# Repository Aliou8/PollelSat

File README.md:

# 

## 📘 Description

Ce projet a pour objectif la conception et la réalisation complète d’un CubeSat au format **1U**.
Il couvre l’ensemble du cycle de développement :

* **Conception 3D** de la structure
* **Développement hardware** (cartes, alimentation, capteurs, communication)
* **Développement software** embarqué
* Intégration, tests et documentation

L’objectif est de créer une plateforme expérimentale ouverte, évolutive et accessible.

---

## 🛰️ Objectifs du projet

* Développer une architecture CubeSat fonctionnelle en open-source
* Expérimenter l’ingénierie spatiale à petite échelle
* Créer un modèle reproductible pour étudiants et makers
* Documenter toutes les étapes : mécanique, électronique, firmware, protocoles…

---

## 🧩 Structure du dépôt

```
/3D/              → Fichiers de conception mécanique (CAD)
/hardware/        → Schémas, PCB, BOM
/software/        → Code embarqué, drivers, protocoles
/docs/            → Documentation technique
/tests/           → Scripts et procédures de tests
```

---

## 🛠️ Technologies utilisées

### Conception 3D
La conception mécanique du CubeSat 1U est entièrement réalisée sur **Onshape**. Dans un premier temps, il est nécessaire de créer le cadre qui respecte les contraintes du CubeSat (voir la [spécification CubeSat](docs/CubeSatSpecification.pdf)).
# 

### 🔧 Hardware

* Microcontrôleur **STM32H7** et **Raspberry PI CM4**
* Capteurs IMU, caméras et modules de télécommunication
* Systèmes d’alimentation **Battery** + **PV**
   | Composant       | Png | Schéma      |
  |:-----------|:---:|------------:|
  |  EPS     |   | [Kicad_sch](hardware/EPS/eps.pdf) |
  |  Battery     |   | [Kicad_sch](hardware/BatteryConnector/BatteryConnector.pdf) |

* Systeme Radio **CC1312R1** à 915 MHz
  | Composant       | Png | Schéma      |
  |:-----------|:---:|------------:|
  |  Radio   |   | [Kicad_sch](hardware/RADIO/radio.pdf) |

### 💻 Software

* Firmware en C/C++
* Outils de simulation
* Protocoles de communication embarqués

---

## 📝 Roadmap

* [ ] Conception complète mécanique 1U
* [ ] Prototype des premiers PCB
* [ ] Développement firmware de base
* [ ] Système de télécommunication minimal
* [ ] Tests thermiques & vibration

---

## 🤝 Contribution

Les contributions sont les bienvenues !
Merci de suivre les pull requests et issues du dépôt.

---

## 📜 Licence

**GNU GPL v3**
Ce projet est open-source et distribué sous licence GNU GPL version 3.
Vous êtes libre de l’utiliser, le modifier et le redistribuer tant que la licence reste préservée.

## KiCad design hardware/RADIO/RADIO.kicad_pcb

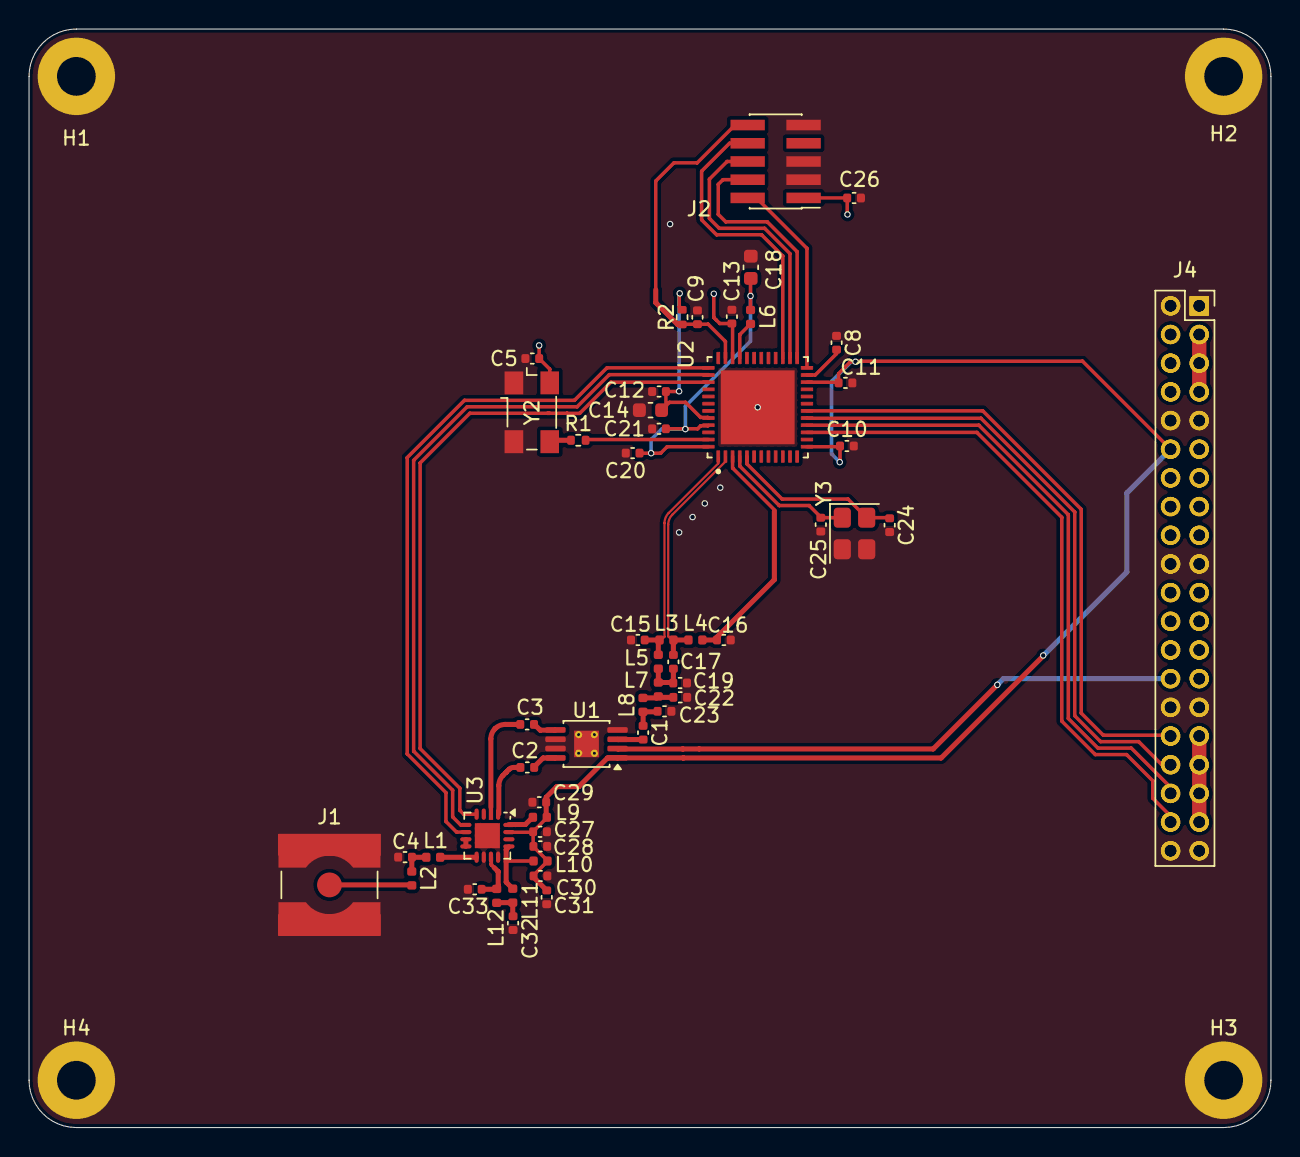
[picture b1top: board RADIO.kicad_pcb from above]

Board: 2 copper layers, 86.6 x 76.6 mm, 58 parts (1 on the bottom side), 60 nets.

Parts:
C1, C2, C3, C16: 100p; C_0402_1005Metric
C4, C33: 2.4p; C_0402_1005Metric
C5, C8, C9, C10, C11, C12, C13, C20, C21, C24, C25, C26: 0.1u; C_0402_1005Metric
C14, C18: 22u; C_0603_1608Metric
C15, C17: 3.6p; C_0402_1005Metric
C19: 2.7p; C_0402_1005Metric
C22: 6.2p; C_0402_1005Metric
C23: 3p; C_0402_1005Metric
C27, C30: 4.7u; C_0402_1005Metric
C28: 10n; C_0402_1005Metric
C29: 120p; C_0402_1005Metric
C31: 33p; C_0402_1005Metric
C32: 10p; C_0402_1005Metric
H1, H2, H3, H4: MountingHole_Pad; MountingHole_2.7mm_M2.5_Pad
J1: SMA ANT; SMA_Amphenol_132134-10_Vertical
J2: Conn_ARM_JTAG_SWD_10; PinHeader_2x05_P1.27mm_Vertical_SMD
J3: Conn; PinHeader_2x20_P2.00mm_Vertical
J4: Conn; PinSocket_2x20_P2.00mm_Vertical
L1, L2: 5.6n; L_0402_1005Metric
L3: 27n; L_0402_1005Metric
L4, L5: 7.5n; L_0402_1005Metric
L6, L7, L8, L10: 6.8n; L_0402_1005Metric
L9: 0.6n; L_0402_1005Metric
L11, L12: 2.7n; L_0402_1005Metric
R1: 100; R_0402_1005Metric
R2: 10K; R_0402_1005Metric
U1: MASWSS0178; MSOP-8-1EP_3x3mm_P0.65mm_EP1.73x1.85mm_ThermalVias
U2: CC1312R1F3RGZT; QFN50P700X700X100-49N
U3: SKY66420-11; UQFN-16-1EP_3x3mm_P0.5mm_EP1.75x1.75mm
Y2: FT5HN; Oscillator_SMD_Fox_FT5H_5.0x3.2mm
Y3: 32.768kHz; Crystal_SMD_3225-4Pin_3.2x2.5mm

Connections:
+3.3V: J3.3, J3.5, J3.7, J4.3, J4.5, J4.7
+5V: J3.31, J3.33, J3.35, J3.37, J4.31, J4.33, J4.35, J4.37
/Clock Oscillator/Clock_in: R1.2, U2.47 (X48M_P)
/Front-End Module/ANT: L1.1, U3.9 (ANT)
/Front-End Module/CPS: U2.38 (DIO_25), U3.5 (CPS)
/Front-End Module/CSD: U2.39 (DIO_26), U3.4 (CSD)
/Front-End Module/CTX: U2.37 (DIO_24), U3.6 (CTX)
/Front-End Module/RX: C3.2, U3.2 (RX)
/Front-End Module/TX: C2.2, U3.1 (TX)
/Front-End Module/TX_IN: C33.2, L12.2, U3.11 (TX_IN)
/INTER CONNECTOR/Pin_2b: J3.4, J4.4
/INTER CONNECTOR/Pin_3b: J3.6, J4.6
/INTER CONNECTOR/Pin_4b: J3.8, J4.8
/INTER CONNECTOR/Pin_6a: J3.11, J4.11
/INTER CONNECTOR/Pin_7a: J3.13, J4.13
/INTER CONNECTOR/Pin_7b: J3.14, J4.14
/INTER CONNECTOR/Pin_8a: J3.15, J4.15
/INTER CONNECTOR/Pin_8b: J3.16, J4.16
/INTER CONNECTOR/Pin_9a: J3.17, J4.17
/INTER CONNECTOR/Pin_9b: J3.18, J4.18
/INTER CONNECTOR/Pin_11a: J3.21, J4.21
/INTER CONNECTOR/Pin_11b: J3.22, J4.22
/INTER CONNECTOR/Pin_12a: J3.23, J4.23
/INTER CONNECTOR/Pin_12b: J3.24, J4.24
/INTER CONNECTOR/Pin_13a: J3.25, J4.25
/INTER CONNECTOR/Pin_13b: J3.26, J4.26
/INTER CONNECTOR/Pin_14a: J3.27, J4.27
/INTER CONNECTOR/Pin_16b: J3.32, J4.32, U2.18 (DIO_12)
/INTER CONNECTOR/Pin_17b: J3.34, J4.34, U2.17 (DIO_11)
/INTER CONNECTOR/Pin_18b: J3.36, J4.36, U2.16 (DIO_1O)
/INTER CONNECTOR/Pin_19b: J3.38, J4.38, U2.15 (DIO_9)
/JTAG/JTAG_TCKC: J2.4 (SWCLK/TCK), U2.25 (JTAG_TCKC)
/JTAG/JTAG_TDI: J2.8 (NC/TDI), U2.27 (DIO_17)
/JTAG/JTAG_TDO: J2.6 (SWO/TDO), U2.26 (DIO_16)
/JTAG/JTAG_TMSC: J2.2 (SWDIO/TMS), U2.24 (JTAG_TMSC)
/JTAG/RESET: C9.1, J2.10 (~RESET), R2.1, U2.35 (RESET_N)
/RD_3.3V: C5.1, C10.1, C11.1, C12.1, C13.1, C14.1, C26.1, C27.2, C28.2, C29.2, C30.1, C31.1, J2.1 (VTref), J3.12, J4.12, L9.1, L10.1, R2.2, U1.1 (CTL1), U2.13 (VDDSZ), U2.22 (VDD83), U2.34 (VDDS_DCDC), U2.44 (VDDS), U3.15 (VCCO), Y2.4 (VDD)
/RF_CTRL: J3.28, J4.28, U1.2 (CTL2)
/Transceiver RF/DCDC_SW: L6.1, U2.33 (DCDC_SW)
/Transceiver RF/RF_N: C17.2, L3.2, L4.1, U2.2 (RF_N)
/Transceiver RF/RF_P: C15.1, L3.1, L5.2, U2.1 (RF_P)
/Transceiver RF/RF_SIGNAL: C1.1, C23.1, L8.1
/Transceiver RF/VDDR: C18.1, C20.1, C21.1, L6.2, U2.45 (VDDR), U2.48 (VDDR_RF)
/Transceiver RF/x32_in: C25.1, U2.4 (X32K_Q1), Y3.1
/Transceiver RF/x32_out: C24.1, U2.5 (X32K_Q2), Y3.4
GND: C4.1, C5.2, C8.1, C9.2, C10.2, C11.2, C12.2, C13.2, C14.2, C15.2, C16.2, C18.2, C19.2, C20.2, C21.2, C22.2, C23.2, C24.2, C25.2, C26.2, C27.1, C28.1, C29.1, C30.2, C31.2, C32.1, C33.1, H1.1, H2.1, H3.1, H4.1, J1.2 (Ext), J2.3 (GND), J2.5 (GND), J2.9 (GNDDetect), J3.1, J3.2, J3.9, J3.10, J3.19, J3.20, J3.29, J3.30, J3.39, J3.40, J4.1, J4.2, J4.9, J4.10, J4.19, J4.20, J4.29, J4.30, J4.39, J4.40, U1.4 (GND), U1.6 (GND), U1.7 (GND), U1.9 (GND), U2.49 (PAD), U3.10 (GND), U3.12 (GND), U3.17 (PAD), Y2.1 (GND), Y2.2 (GND), Y3.2, Y3.3
unnamed: C4.2, L1.2, L2.1
unnamed: C17.1, C19.1, L5.1, L7.2
unnamed: C22.1, L7.1, L8.2
unnamed: C32.2, L11.2, L12.1
unnamed: J1.1 (In), L2.2
unnamed: C2.1, U1.8 (RF1)
unnamed: C3.1, U1.5 (RF2)
unnamed: C1.2, U1.3 (RFC)
unnamed: C8.2, U2.23 (DCOUPL)
unnamed: C16.1, L4.2, U2.3 (RX_TX)
unnamed: U3.7 (LNA_IN), U3.8 (RX_FLT)
unnamed: L10.2, L11.1, U3.13 (PA_OUT)
unnamed: L9.2, U3.16 (VCC1)
unnamed: R1.1, Y2.3 (OUT)

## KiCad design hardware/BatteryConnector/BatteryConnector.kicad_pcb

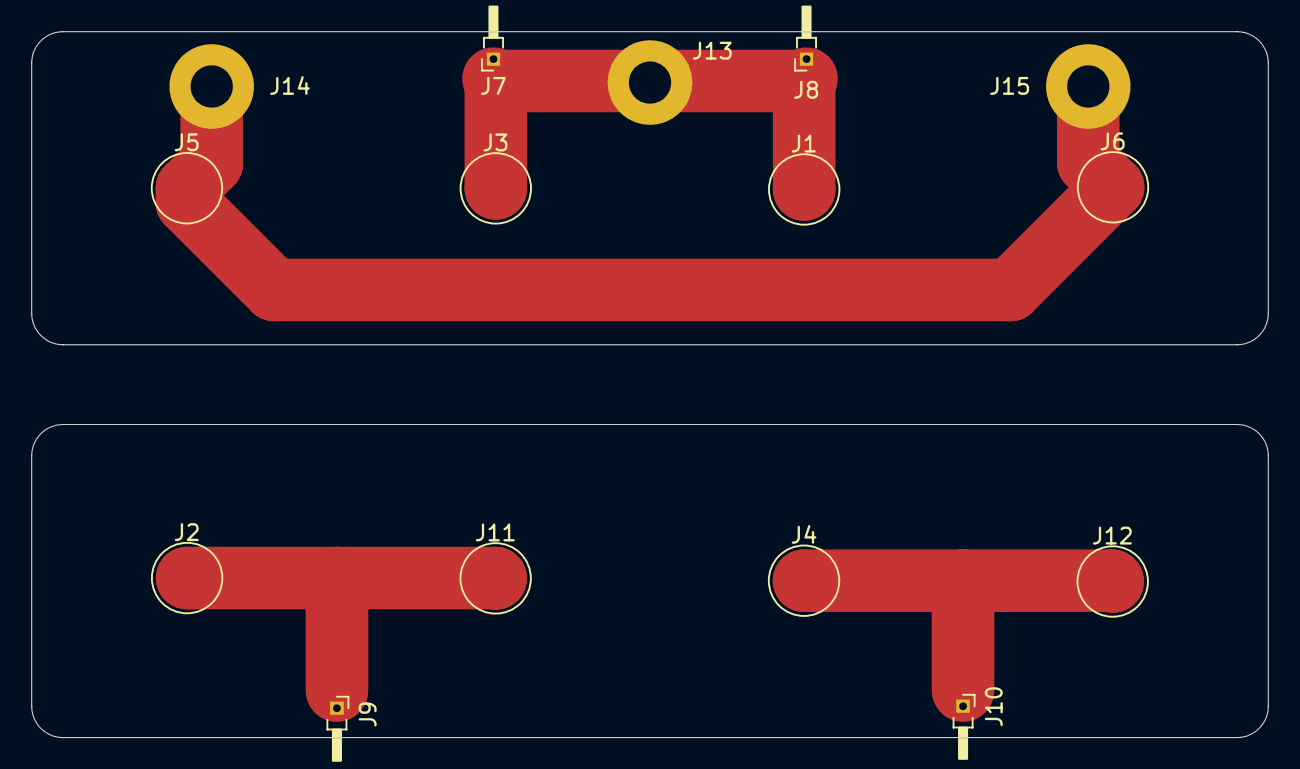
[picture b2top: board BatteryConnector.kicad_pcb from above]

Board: 2 copper layers, 79.0 x 45.1 mm, 15 parts (0 on the bottom side), 4 nets.

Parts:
J1: c1; TestPoint_Pad_D4.0mm
J2, J11: c2; TestPoint_Pad_D4.0mm
J3: c3; TestPoint_Pad_D4.0mm
J4, J12: c4; TestPoint_Pad_D4.0mm
J5: gnd1; TestPoint_Pad_D4.0mm
J6: gnd2; TestPoint_Pad_D4.0mm
J7, J8, J9, J10: conn; PinHeader_1x01_P1.00mm_Horizontal
J13, J14, J15: INtConn; MountingHole_2.7mm_M2.5_Pad

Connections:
+BATT: J1.1, J3.1, J7.1, J8.1, J13.1
-BATT: J5.1, J6.1, J14.1, J15.1
unnamed: J4.1, J10.1, J12.1
unnamed: J2.1, J9.1, J11.1

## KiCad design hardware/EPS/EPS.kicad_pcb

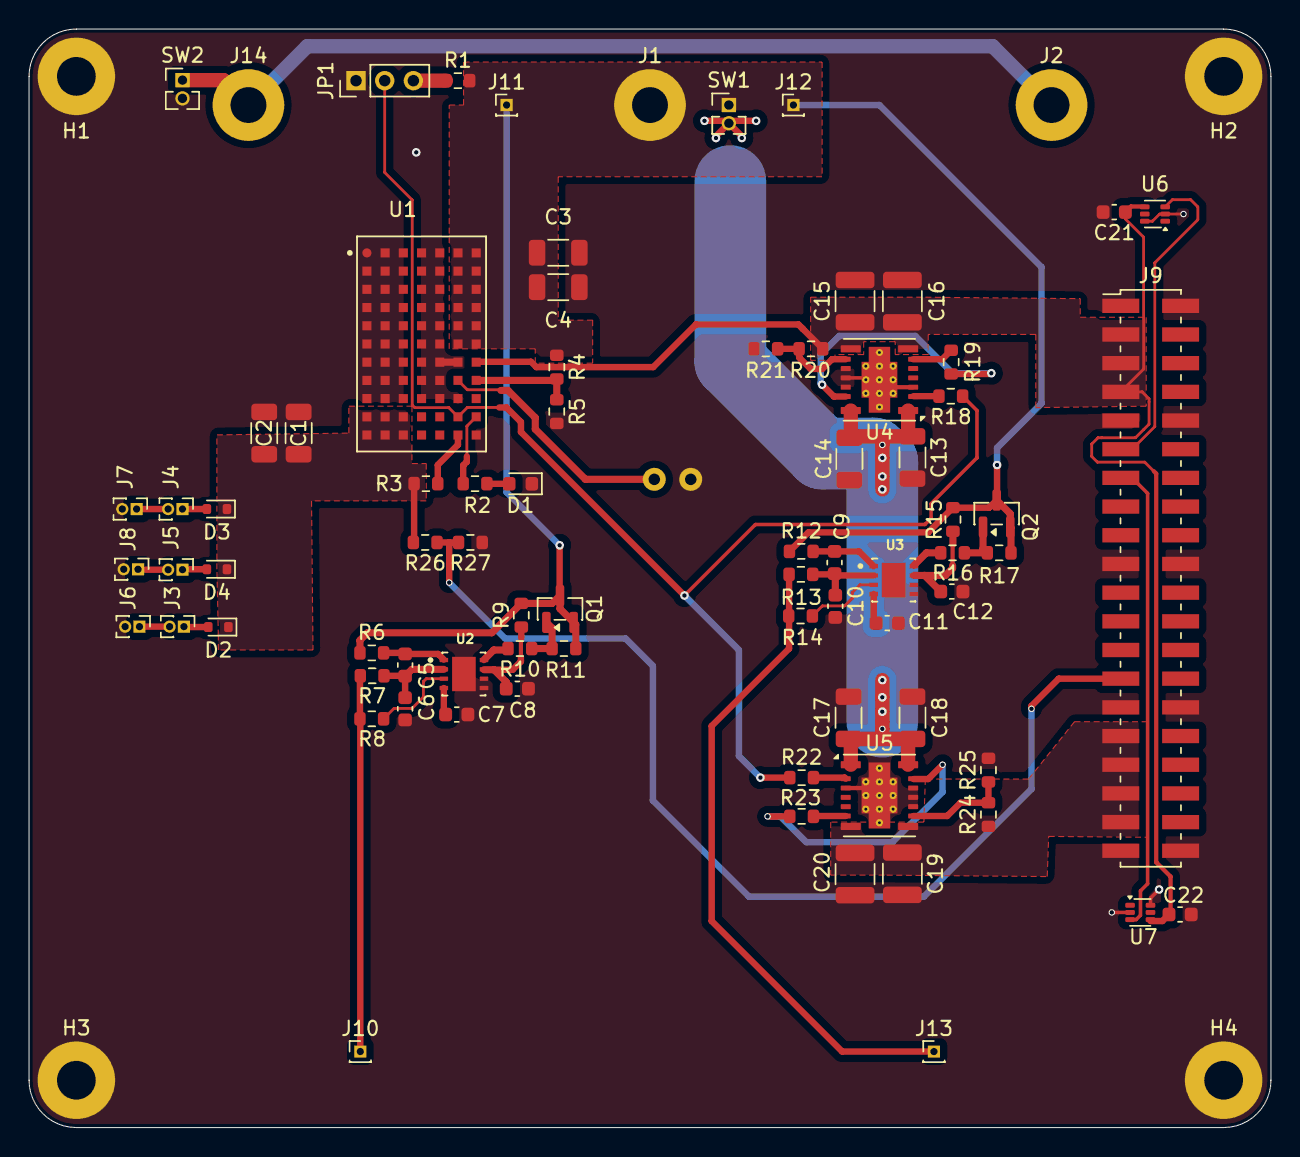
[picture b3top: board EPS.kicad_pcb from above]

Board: 2 copper layers, 86.6 x 76.6 mm, 84 parts (1 on the bottom side), 47 nets.

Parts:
C1, C2, C3, C4: 22u; C_1206_3216Metric
C5, C6, C9, C10, C21, C22: 0.1u; C_0603_1608Metric
C7, C8, C11, C12: 0.33u; C_0603_1608Metric
C13, C14, C17, C18: 10u; C_1206_3216Metric
C15, C16, C19, C20: 47u; C_1210_3225Metric
D1: LED_CH; LED_0603_1608Metric
D2, D3, D4: ESD5Zxx; D_SOD-523
H1, H2, H3, H4: MountingHole_Pad; MountingHole_2.7mm_M2.5_Pad
J1, J2, J14: Conn; MountingHole_2.5mm_Pad
J3, J4, J5, J6, J7, J8: PV; PinHeader_1x02_P1.00mm_Vertical
J9: Conn; PinHeader_2x20_P2.00mm_Vertical_SMD
J10, J11, J12, J13: vc; PinHeader_1x01_P1.00mm_Vertical
JP1: RBF; PinHeader_1x03_P2.00mm_Vertical
Q1, Q2: DMP3099L; SOT-23
R1, R18, R19, R22, R23: 100k; R_0603_1608Metric
R2, R26, R27: 1k; R_0603_1608Metric
R3: 312k; R_0603_1608Metric
R4: 549k; R_0603_1608Metric
R5: 459k; R_0603_1608Metric
R6, R7, R8, R12, R13, R14: 2.2k; R_0603_1608Metric
R9, R10, R11, R15, R16, R17: 1K; R_0603_1608Metric
R20, R24: 10k; R_0603_1608Metric
R21: 4.32k; R_0603_1608Metric
R25: 2.49k; R_0603_1608Metric
SW1, SW2: SW_DEPLOY; PinHeader_1x02_P1.27mm_Vertical
TH1: NTC 10k; R_LDR_4.9x4.2mm_P2.54mm_Vertical
U1: LTM8062IV_PBF; IC_LTM8062IV_PBF
U2, U3: BQ29209DRBT; IC_BQ29209DRBT
U4, U5: TPSM53604RDA; Texas_B3QFN-14-1EP_5x5.5mm_P0.65mm_ThermalVia
U6, U7: TMP20AIDRL; SOT-563

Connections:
+3.3V: C15.1, C16.1, C21.1, C22.1, J9.3, J9.5, J9.7, R20.1, U1.G7 (BIAS), U4.7 (VOUT), U4.8 (VOUT), U6.4 (V_{DD}), U7.4 (V_{DD})
+5V: C19.1, C20.1, J9.31, J9.33, J9.35, J9.37, R24.1, U5.7 (VOUT), U5.8 (VOUT)
+BATT: C3.1, C4.1, J1.1, J11.1, J12.1, Q1.2 (S), Q1.3 (D), Q2.2 (S), Q2.3 (D), R1.2, R4.1, R6.1, R9.2, R11.2, R12.1, R15.2, R17.2, SW1.1 (A), U1.A6 (BAT), U1.A7 (BAT), U1.B6 (BAT), U1.B7 (BAT), U1.C6 (BAT), U1.C7 (BAT), U1.D6 (BAT), U1.D7 (BAT), U1.E6 (BAT), U1.E7 (BAT), U1.F6 (BAT), U1.F7 (BAT)
-BATT: J2.1, J14.1, SW2.1 (A)
/3.3V BUCK/VIN: C13.1, C14.1, C17.1, C18.1, SW1.2 (B), U4.1 (VIN), U4.14 (VIN), U5.1 (VIN), U5.14 (VIN)
/ADC_SOLAR: J9.27, R26.1, R27.2
/Battery Charger/VPV: C1.1, C2.1, D2.1 (K), D3.1 (K), D4.1 (K), R3.1, R26.2, U1.K1 (VIN), U1.K2 (VIN), U1.K3 (VIN), U1.L1 (VIN), U1.L2 (VIN), U1.L3 (VIN)
/Battery Charger/~CHRG: R2.1, U1.K7 (~CHRG)
/NTC: TH1.1, U1.H6 (NTC)
/Protection1/Cell1: J13.1, R13.1, R14.1
/Protection/Cell1: J10.1, R7.1, R8.1
/RBF: JP1.2 (C), R18.1, R22.1, U1.K6 (RUN)
/TMP_ADC1: J9.11, U6.3 (V_{OUT})
/TMP_ADC2: J9.13, U7.3 (V_{OUT})
GND: C1.2, C2.2, C3.2, C4.2, C6.2, C7.2, C8.2, C10.2, C11.2, C12.2, C13.2, C14.2, C15.2, C16.2, C17.2, C18.2, C19.2, C20.2, C21.2, C22.2, D1.1 (K), H1.1, H2.1, H3.1, H4.1, J6.2, J7.2, J8.2, J9.1, J9.2, J9.9, J9.10, J9.19, J9.20, J9.29, J9.30, J9.39, J9.40, JP1.1 (A), R5.2, R21.2, R25.2, R27.1, SW2.2 (B), TH1.2, U1.A1 (GND), U1.A2 (GND), U1.A3 (GND), U1.A4 (GND), U1.A5 (GND), U1.B1 (GND), U1.B2 (GND), U1.B3 (GND), U1.B4 (GND), U1.B5 (GND), U1.C1 (GND), U1.C2 (GND), U1.C3 (GND), U1.C4 (GND), U1.C5 (GND), U1.D1 (GND), U1.D2 (GND), U1.D3 (GND), U1.D4 (GND), U1.D5 (GND), U1.E1 (GND), U1.E2 (GND), U1.E3 (GND), U1.E4 (GND), U1.E5 (GND), U1.F1 (GND), U1.F2 (GND), U1.F3 (GND), U1.F4 (GND), U1.F5 (GND), U1.G1 (GND), U1.G2 (GND), U1.G3 (GND), U1.G4 (GND), U1.G5 (GND), U1.G6 (GND), U1.H1 (GND), U1.H2 (GND), U1.H3 (GND), U1.H4 (GND), U1.H5 (GND), U1.J1 (GND), U1.J2 (GND), U1.J3 (GND), U1.J4 (GND), U1.J5 (GND), U1.J6 (TMR), U1.L7 (GND), U2.5 (GND), U2.6 (~CB_EN), U2.9 (PWR_PAD), U3.5 (GND), U3.6 (~CB_EN), U3.9 (PWR_PAD), U4.3 (PGND), U4.10 (PGND), U4.11 (PGND), U4.12 (AGND), U4.15 (PGND), U5.3 (PGND), U5.10 (PGND), U5.11 (PGND), U5.12 (AGND), U5.15 (PGND), U6.2 (GND), U6.6 (GND), U7.2 (GND), U7.6 (GND)
unnamed: D1.2 (A), R2.2
unnamed: D2.2 (A), J3.1
unnamed: D3.2 (A), J4.1
unnamed: D4.2 (A), J5.1
unnamed: J3.2, J6.1
unnamed: J4.2, J7.1
unnamed: J5.2, J8.1
unnamed: JP1.3 (B), R1.1
unnamed: Q1.1 (G), R10.1, R11.1
unnamed: Q2.1 (G), R16.1, R17.1
unnamed: R4.2, R5.1, U1.H7 (ADJ)
unnamed: R3.2, U1.L6 (VINREG)
unnamed: C7.1, U2.4 (CD)
unnamed: R10.2, U2.8 (OUT)
unnamed: C5.2, C6.1, R7.2, U2.2 (VC1)
unnamed: R8.2, U2.3 (VC1_CB)
unnamed: C5.1, R6.2, U2.1 (VC2)
unnamed: C8.1, R9.1, U2.7 (VDD)
unnamed: C11.1, U3.4 (CD)
unnamed: R16.2, U3.8 (OUT)
unnamed: C9.2, C10.1, R13.2, U3.2 (VC1)
unnamed: R14.2, U3.3 (VC1_CB)
unnamed: C9.1, R12.2, U3.1 (VC2)
unnamed: C12.1, R15.1, U3.7 (VDD)
unnamed: R18.2, U4.2 (EN)
unnamed: R20.2, R21.1, U4.9 (FB)
unnamed: R19.2, U4.6 (PGOOD)
unnamed: R19.1, U4.13 (V5V)
unnamed: R22.2, U5.2 (EN)
unnamed: R24.2, R25.1, U5.9 (FB)
unnamed: R23.2, U5.6 (PGOOD)
unnamed: R23.1, U5.13 (V5V)

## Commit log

2025-11-29 logo
2025-11-29 Ajout de FaceVP
2025-11-29 Add 3D design section to README
    Added section on 3D design using Onshape.
2025-11-29 Include image of 3D frame in README
    Added image reference for 3D design of CubeSat.
2025-11-29 Add FacePV3D image reference to README
    Added image reference for FacePV3D in the 3D conception section.
2025-11-29 Combine image tags in README.md
2025-11-29 Supp hardware
2025-11-29 Ajout sch pdf png
2025-11-29 Update README with hardware components and schematics
    Added hardware components table and images to README.

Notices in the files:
README.md:
License: GNU GPL v3
